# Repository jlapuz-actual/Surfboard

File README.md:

---
I mean for this to be a keyboard PCB that you can drop in an [Adafruit Bluetooth Feather](https://www.adafruit.com/product/2829), switches, and diodes.

Layout  
---
[Layout with intended keycaps to use](http://www.keyboard-layout-editor.com/#/gists/e4e8a6f66c2c640a77dbacd3e51fc3d9)  
I wanted a 40% to use with a phone or tablet but with more function and modifier keys that are wider than 1u. In addition I wanted to be able to use keys from a 60% percent at minimum, although limited to DSA, G20, SA R3, and similar sets if contoured keys in the wrong row is a problem  

[Layer 0](http://www.keyboard-layout-editor.com/#/gists/cc1070f71789ace71d15d57b2ea0d759)  
This is default layer  

---
These are the function layers. What I tried to do is put the modified keys on the opposite side of the activating function key. The way I use modifier keys means that I press the modifier key with one hand and type with the other.  
[Layer 1](http://www.keyboard-layout-editor.com/#/gists/59b77285f404e8a5413cfdc76923d688)  
Math layer  
[Layer 2](http://www.keyboard-layout-editor.com/#/gists/df4af78e93a107d80d330e3a977cecf1)  
Navigation  
[Layer 3](http://www.keyboard-layout-editor.com/#/gists/67db6d858fd3169d8e3274208c5a3cfd)  
F keys  
These are all stuff to do in code, but this is what is planned.  

PCB  
---    

None of this is final, partly because I don't know if it's aligned correctly and if there is an egregious electrical error
[keyswitch.brd](https://github.com/jlapuz-actual/Surfboard/blob/master/keyswitch.pdf)  |  [keyswitch.sch](https://github.com/jlapuz-actual/Surfboard/blob/master/keyswitchsch.pdf)    
Basically I have no idea if the routes are "legal". I'm pretty sure that the schematic is correct though.  
Regardless I need a few more experienced sets of eyes, since I'm pretty much shooting blind.  

---  

I may change the position of the feather but it will definitely have the usb port facing the outside edge, most likely the left and right edges, as it serves as the charger port for the battery that will be connected.  

[keyswitch_matrixOnly.brd](https://github.com/jlapuz-actual/Surfboard/blob/master/keyswitch_matrixOnly.pdf) and [keyswitch_noRoutes.brd](https://github.com/jlapuz-actual/Surfboard/blob/master/keyswitch_noRoutes.pdf) are checkpoint backups.   
  
All of these are Eagle files, I am looking into converting the files for use in Kicad.  

Thoughts  
---  

I didn't plan on Alps support since there isn't much keycap support for Alps, and I don't find contoured keycaps in the wrong rows attractive. I didn't find a component in the [clueboard eagle library](https://github.com/skullydazed/clueboard_eagle) with alps-mx mount that has a integrated diode footprint, but I may be able to put something together. If I do go on and complete this project, I plan on writing my own firmware since for me that would be the primary purpose, to tinker around with the code, and that will be uploaded here. As I understand,[qmk firmware](https://github.com/qmk/qmk_firmware) is perfectly usable on the Adafruit Bluefruit Feather, so if anyone wants to use these files to order their own pcb, the keyboard itself is not dependent on me to create firmware for it.

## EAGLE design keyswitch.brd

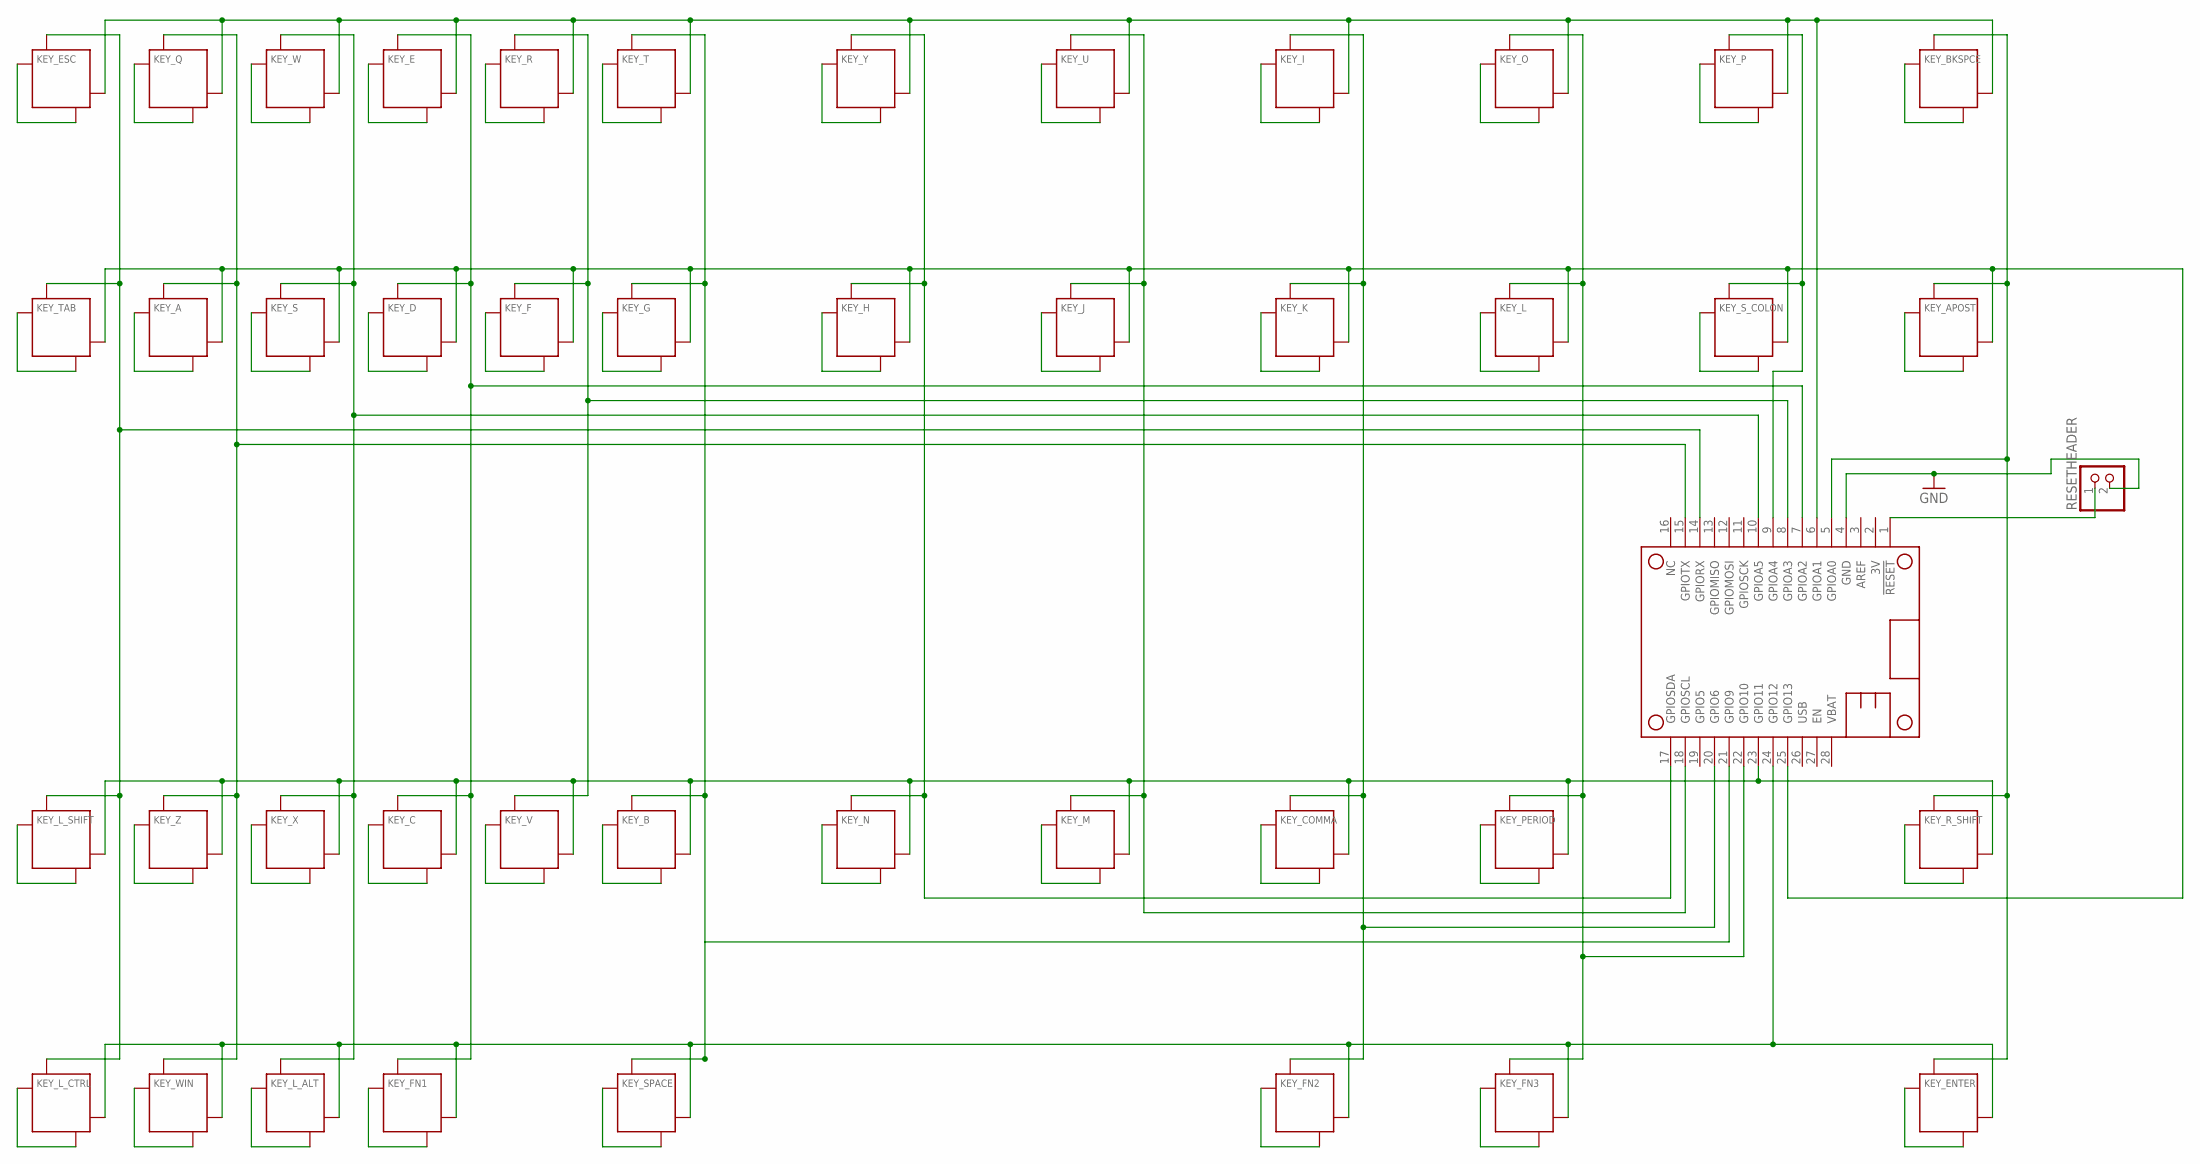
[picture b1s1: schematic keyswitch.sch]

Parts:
FEATHER: FEATHERWING_NODIM; FEATHERWING_DIM
KEY_A: KEYSWITCH-DIODE-MX-1U-DIODE; MX-1U-DIODE
KEY_APOST: KEYSWITCH-DIODE-MX-1U-DIODE; MX-1U-DIODE
KEY_B: KEYSWITCH-DIODE-MX-1U-DIODE; MX-1U-DIODE
KEY_BKSPCE: KEYSWITCH-DIODE-MX-1U-DIODE; MX-1U-DIODE
KEY_C: KEYSWITCH-DIODE-MX-1U-DIODE; MX-1U-DIODE
KEY_COMMA: KEYSWITCH-DIODE-MX-1U-DIODE; MX-1U-DIODE
KEY_D: KEYSWITCH-DIODE-MX-1U-DIODE; MX-1U-DIODE
KEY_E: KEYSWITCH-DIODE-MX-1U-DIODE; MX-1U-DIODE
KEY_ENTER: KEYSWITCH-DIODE-MX-1U-DIODE; MX-1U-DIODE
KEY_ESC: KEYSWITCH-DIODE-MX-1U-DIODE; MX-1U-DIODE
KEY_F: KEYSWITCH-DIODE-MX-1U-DIODE; MX-1U-DIODE
KEY_FN1, KEY_FN2, KEY_FN3: KEYSWITCH-DIODE-MX-1U-DIODE; MX-1U-DIODE
KEY_G: KEYSWITCH-DIODE-MX-1U-DIODE; MX-1U-DIODE
KEY_H: KEYSWITCH-DIODE-MX-1U-DIODE; MX-1U-DIODE
KEY_I: KEYSWITCH-DIODE-MX-1U-DIODE; MX-1U-DIODE
KEY_J: KEYSWITCH-DIODE-MX-1U-DIODE; MX-1U-DIODE
KEY_K: KEYSWITCH-DIODE-MX-1U-DIODE; MX-1U-DIODE
KEY_L: KEYSWITCH-DIODE-MX-1U-DIODE; MX-1U-DIODE
KEY_L_ALT: KEYSWITCH-DIODE-MX-1U-DIODE; MX-1U-DIODE
KEY_L_CTRL: KEYSWITCH-DIODE-MX-1U-DIODE; MX-1U-DIODE
KEY_L_SHIFT: KEYSWITCH-DIODE-MX-1U-DIODE; MX-1U-DIODE
KEY_M: KEYSWITCH-DIODE-MX-1U-DIODE; MX-1U-DIODE
KEY_N: KEYSWITCH-DIODE-MX-1U-DIODE; MX-1U-DIODE
KEY_O: KEYSWITCH-DIODE-MX-1U-DIODE; MX-1U-DIODE
KEY_P: KEYSWITCH-DIODE-MX-1U-DIODE; MX-1U-DIODE
KEY_PERIOD: KEYSWITCH-DIODE-MX-1U-DIODE; MX-1U-DIODE
KEY_Q: KEYSWITCH-DIODE-MX-1U-DIODE; MX-1U-DIODE
KEY_R: KEYSWITCH-DIODE-MX-1U-DIODE; MX-1U-DIODE
KEY_R_SHIFT: KEYSWITCH-DIODE-MX-1U-DIODE; MX-1U-DIODE
KEY_S: KEYSWITCH-DIODE-MX-1U-DIODE; MX-1U-DIODE
KEY_SPACE: KEYSWITCH-DIODE-MX-1U-DIODE; MX-1U-DIODE
KEY_S_COLON: KEYSWITCH-DIODE-MX-1U-DIODE; MX-1U-DIODE
KEY_T: KEYSWITCH-DIODE-MX-1U-DIODE; MX-1U-DIODE
KEY_TAB: KEYSWITCH-DIODE-MX-1U-DIODE; MX-1U-DIODE
KEY_U: KEYSWITCH-DIODE-MX-1U-DIODE; MX-1U-DIODE
KEY_V: KEYSWITCH-DIODE-MX-1U-DIODE; MX-1U-DIODE
KEY_W: KEYSWITCH-DIODE-MX-1U-DIODE; MX-1U-DIODE
KEY_WIN: KEYSWITCH-DIODE-MX-1U-DIODE; MX-1U-DIODE
KEY_X: KEYSWITCH-DIODE-MX-1U-DIODE; MX-1U-DIODE
KEY_Y: KEYSWITCH-DIODE-MX-1U-DIODE; MX-1U-DIODE
KEY_Z: KEYSWITCH-DIODE-MX-1U-DIODE; MX-1U-DIODE
RESETHEADER: PINHD-1X2; 1X02

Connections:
GND: FEATHER.4 (GND), RESETHEADER.2
unnamed: KEY_ESC.D+, KEY_ESC.MX1 (P0)
unnamed: KEY_Q.D+, KEY_Q.MX1 (P0)
unnamed: KEY_W.D+, KEY_W.MX1 (P0)
unnamed: KEY_E.D+, KEY_E.MX1 (P0)
unnamed: KEY_R.D+, KEY_R.MX1 (P0)
unnamed: KEY_T.D+, KEY_T.MX1 (P0)
unnamed: KEY_Y.D+, KEY_Y.MX1 (P0)
unnamed: KEY_U.D+, KEY_U.MX1 (P0)
unnamed: KEY_I.D+, KEY_I.MX1 (P0)
unnamed: KEY_O.D+, KEY_O.MX1 (P0)
unnamed: KEY_P.D+, KEY_P.MX1 (P0)
unnamed: KEY_BKSPCE.D+, KEY_BKSPCE.MX1 (P0)
unnamed: KEY_TAB.D+, KEY_TAB.MX1 (P0)
unnamed: KEY_A.D+, KEY_A.MX1 (P0)
unnamed: KEY_S.D+, KEY_S.MX1 (P0)
unnamed: KEY_D.D+, KEY_D.MX1 (P0)
unnamed: KEY_F.D+, KEY_F.MX1 (P0)
unnamed: KEY_G.D+, KEY_G.MX1 (P0)
unnamed: KEY_H.D+, KEY_H.MX1 (P0)
unnamed: KEY_J.D+, KEY_J.MX1 (P0)
unnamed: KEY_K.D+, KEY_K.MX1 (P0)
unnamed: KEY_L.D+, KEY_L.MX1 (P0)
unnamed: KEY_S_COLON.D+, KEY_S_COLON.MX1 (P0)
unnamed: KEY_APOST.D+, KEY_APOST.MX1 (P0)
unnamed: KEY_L_SHIFT.D+, KEY_L_SHIFT.MX1 (P0)
unnamed: KEY_Z.D+, KEY_Z.MX1 (P0)
unnamed: KEY_X.D+, KEY_X.MX1 (P0)
unnamed: KEY_C.D+, KEY_C.MX1 (P0)
unnamed: KEY_V.D+, KEY_V.MX1 (P0)
unnamed: KEY_B.D+, KEY_B.MX1 (P0)
unnamed: KEY_N.D+, KEY_N.MX1 (P0)
unnamed: KEY_M.D+, KEY_M.MX1 (P0)
unnamed: KEY_COMMA.D+, KEY_COMMA.MX1 (P0)
unnamed: KEY_PERIOD.D+, KEY_PERIOD.MX1 (P0)
unnamed: FEATHER.7 (GPIOA2), KEY_C.MX2 (P1), KEY_D.MX2 (P1), KEY_E.MX2 (P1), KEY_FN1.MX2 (P1)
unnamed: KEY_R_SHIFT.D+, KEY_R_SHIFT.MX1 (P0)
unnamed: KEY_WIN.D+, KEY_WIN.MX1 (P0)
unnamed: KEY_L_ALT.D+, KEY_L_ALT.MX1 (P0)
unnamed: KEY_FN1.D+, KEY_FN1.MX1 (P0)
unnamed: FEATHER.1 (!RESET), RESETHEADER.1
unnamed: KEY_SPACE.D+, KEY_SPACE.MX1 (P0)
unnamed: FEATHER.15 (GPIOTX), KEY_A.MX2 (P1), KEY_Q.MX2 (P1), KEY_WIN.MX2 (P1), KEY_Z.MX2 (P1)
unnamed: FEATHER.10 (GPIOA5), KEY_L_ALT.MX2 (P1), KEY_S.MX2 (P1), KEY_W.MX2 (P1), KEY_X.MX2 (P1)
unnamed: KEY_FN2.D+, KEY_FN2.MX1 (P0)
unnamed: KEY_FN3.D+, KEY_FN3.MX1 (P0)
unnamed: FEATHER.21 (GPIO9), KEY_B.MX2 (P1), KEY_G.MX2 (P1), KEY_SPACE.MX2 (P1), KEY_T.MX2 (P1)
unnamed: KEY_ENTER.D+, KEY_ENTER.MX1 (P0)
unnamed: FEATHER.8 (GPIOA3), KEY_F.MX2 (P1), KEY_R.MX2 (P1), KEY_V.MX2 (P1)
unnamed: FEATHER.24 (GPIO12), KEY_ENTER.D-, KEY_FN1.D-, KEY_FN2.D-, KEY_FN3.D-, KEY_L_ALT.D-, KEY_L_CTRL.D-, KEY_SPACE.D-, KEY_WIN.D-
unnamed: FEATHER.17 (GPIOSDA), KEY_H.MX2 (P1), KEY_N.MX2 (P1), KEY_Y.MX2 (P1)
unnamed: FEATHER.22 (GPIO10), KEY_FN3.MX2 (P1), KEY_L.MX2 (P1), KEY_O.MX2 (P1), KEY_PERIOD.MX2 (P1)
unnamed: FEATHER.20 (GPIO6), KEY_COMMA.MX2 (P1), KEY_FN2.MX2 (P1), KEY_I.MX2 (P1), KEY_K.MX2 (P1)
unnamed: FEATHER.18 (GPIOSCL), KEY_J.MX2 (P1), KEY_M.MX2 (P1), KEY_U.MX2 (P1)
unnamed: FEATHER.9 (GPIOA4), KEY_P.MX2 (P1), KEY_S_COLON.MX2 (P1)
unnamed: FEATHER.5 (GPIOA0), KEY_APOST.MX2 (P1), KEY_BKSPCE.MX2 (P1), KEY_ENTER.MX2 (P1), KEY_R_SHIFT.MX2 (P1)
unnamed: FEATHER.6 (GPIOA1), KEY_BKSPCE.D-, KEY_E.D-, KEY_ESC.D-, KEY_I.D-, KEY_O.D-, KEY_P.D-, KEY_Q.D-, KEY_R.D-, KEY_T.D-, KEY_U.D-, KEY_W.D-, KEY_Y.D-
unnamed: FEATHER.14 (GPIORX), KEY_ESC.MX2 (P1), KEY_L_CTRL.MX2 (P1), KEY_L_SHIFT.MX2 (P1), KEY_TAB.MX2 (P1)
unnamed: FEATHER.23 (GPIO11), KEY_B.D-, KEY_C.D-, KEY_COMMA.D-, KEY_L_SHIFT.D-, KEY_M.D-, KEY_N.D-, KEY_PERIOD.D-, KEY_R_SHIFT.D-, KEY_V.D-, KEY_X.D-, KEY_Z.D-
unnamed: KEY_L_CTRL.D+, KEY_L_CTRL.MX1 (P0)
unnamed: FEATHER.25 (GPIO13), KEY_A.D-, KEY_APOST.D-, KEY_D.D-, KEY_F.D-, KEY_G.D-, KEY_H.D-, KEY_J.D-, KEY_K.D-, KEY_L.D-, KEY_S.D-, KEY_S_COLON.D-, KEY_TAB.D-

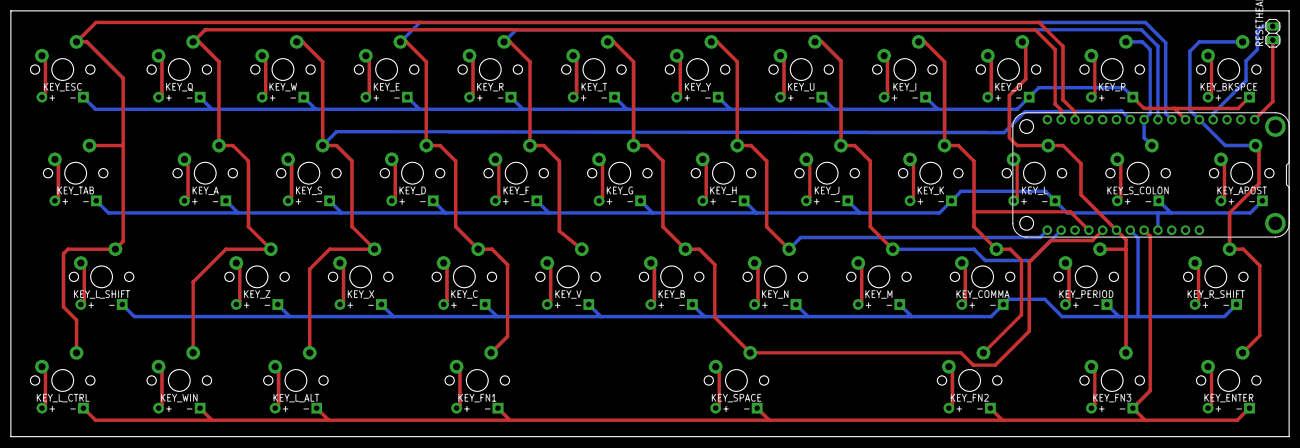
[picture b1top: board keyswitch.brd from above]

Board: 2 copper layers, 234.9 x 78.3 mm, 45 parts (0 on the bottom side), 61 nets.

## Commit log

2017-05-03 first upload
2017-05-03 minor update
2017-05-03 minor update and link fixing
2017-05-03 Create license
2017-05-04 modified to remove vias
2017-05-04 export to pdf
